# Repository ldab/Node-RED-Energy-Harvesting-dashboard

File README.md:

# Node-RED-Energy-Harvesting-dashboard

Node-RED Energy Harvesting dashboard example, weather forecast, temperature and humidty measurement. MQTT, ESP32, u-blox NINA-W10, HTU21D, IBM Cloud, CloudMQTT

## Sumary

1. [How to build PlatformIO based project](/README.md#How-to-build-PlatformIO-based-project)
2. [TODO](/README.md#TODO)
3. [Energy Harvesting](/README.md#Energy-Harvesting)
4. [MQTT Broker](/README.md#MQTT-Broker)
5. [IBM Node-RED Hosting](/README.md#IBM-Node-RED-Hosting)
6. [Node-RED Flow](/README.md#Node-RED-Flow)
7. [OpenWeatherMap API](/README.md#OpenWeatherMap-API)
8. [Node-RED Notification](/README.md#Node-RED-Notification)
9. [Programming](/README.md#Programming)
10. [Calibrating ADC for ESP32](/README.md#Calibrating-ADC-for-ESP32)
11. [Partition Table and Flash size](/README.md#Partition-Table-and-Flash-size)
12. [Erase Flash](/README.md#Erase-Flash)
13. [Power Measurement](/README.md#Power-Measurement)
14. [PCB](/README.md#PCB)
15. [Final Thoughts or Improvements](/README.md#Final-Thoughts-or-Impovements)
16. [Credits](/README.md#Credits)

## How to build PlatformIO based project

* More information can be found on their comprehensive [Docs](https://docs.platformio.org/en/latest/ide/vscode.html). But Basically:

  0. Download and install official Microsoft Visual Studio Code. PlatformIO IDE is built on top of it
  1. **Open** VSCode Package Manager
  2. **Search** for official `platformio-ide` [extension](https://marketplace.visualstudio.com/items?itemName=platformio.platformio-ide)
  3. **Install** PlatformIO IDE.

## TODO

- [x] More detailed IBM deploy;
- [ ] Details on the flows;
- [x] Node to be installed;
- [ ] Energy Harvesting details;

## Energy Harvesting

### Energy Budget

#### While Communicating

Component | ~Typ mA
----------|--------
NINA-W102 |120

#### While Sleep (TPL5110)

Component | ~Typ μA
----------|--------
TPL5110   |0.035
Cap leak  |30
LDO       |1
Passive   |5

* The code takes in average 2000ms to execute;
* Wakes up every hour;
* 10 hours of charging soruce;

## MQTT Broker

The MQTT Broker used is [CloudMQTT](https://www.cloudmqtt.com/) they offer Free accounts 😉 that works just fine.

## IBM Node-RED Hosting

The process was a bit tedious and took a while to get it properly running as of today (2019/06/15) the information provided on the tutorial had few broken links.

[https://nodered.org/docs/platforms/bluemix](https://nodered.org/docs/platforms/bluemix)

1. Sign-up/Log in to [https://cloud.ibm.com/](https://cloud.ibm.com/);
2. Using the top search bar, search for `Node-RED Starter`;
3. Fill the required fields, `App name`, `Host name`, etc...
4. Select `Lite` for `SDK for Node.js` and `Cloudant`, those are free, you can upgrade later if required;
5. Click `Create` at the bottom right, the circle will spin, take few seconds;
6. You will be redirected to the next page and should see `running` when everything is ready for use:

7. Go to your App URL, something like [http://AppName.eu-gb.mybluemix.net](http://AppName.eu-gb.mybluemix.net) and complete the initial set-up;
8. The Node-Red GUI Flow Editor is available at [http://AppName.eu-gb.mybluemix.net/red](http://AppName.eu-gb.mybluemix.net/red)

* After installing the Node desbribed below, Your Node-red Dashboard is available at [http://AppName.eu-gb.mybluemix.net/ui](http://AppName.eu-gb.mybluemix.net/ui)

## Node-RED Flow

### Install required nodes

* Menu -> Manage Palette -> Install tab. You will need `node-red-node-openweathermap` and `node-red-dashboard`

### Import Node example

* Copy the flow below and import to your Nore-RED available at `yournode.eu-gb.mybluemix.net/red` Import > Clipboard, paste it.

You will find the flow.json [here](./Node-RED%20flow/flows.json).

### Cloudant Credentials for cleaning database

* Generally Cloudant autheticate via IBM cloud therefore we need to create new Credentials and use the username and password for authentication on the `delet inputs on database` node.

## OpenWeatherMap API

* In order to get the weather forecast information for the OpenWeatherMap node, you will need to get your API at [https://openweathermap.org/api](https://openweathermap.org/api)
* Then define your location and the information you would like to show on the "Forecast String" node:
```
{
  "coord":{"lon":139,"lat":35},
  "sys":{"country":"JP","sunrise":1369769524,"sunset":1369821049},
  "weather":[{"id":804,"main":"clouds","description":"overcast clouds","icon":"04n"}],
  "main":{"temp":289.5,"humidity":89,"pressure":1013,"temp_min":287.04,"temp_max":292.04},
  "wind":{"speed":7.31,"deg":187.002},
  "rain":{"3h":0},
  "clouds":{"all":92},
  "dt":1369824698,
  "id":1851632,
  "name":"Shuzenji",
  "cod":200
}
```

## Node-RED Notification

* Via the `catch` node, you can enable notification, for your phone for example. Below I have quickly show few options:

1. Email

  * Use the `email` output, configured with your email provider info;

2. PushSafer

  * Offers several customizations, sound, vibration, icons, etc:
  * GET request url: `https://www.pushsafer.com/api?k=YOURKEY&c=%23ff0000&v=1&a=1&m={{payload}}`

5. Twilio SMS

  * SMS API, built-in to the Node-RED and IBM example;

6. IFTT

  * If this than that, with android and iOS apps can be accesible via webhooks;
  * GET `https://maker.ifttt.com/trigger/YOUR_EVENT/with/key/YOUR_KEY?value1=MESSAGE`

## NINA-W1 Programming

* An external 3.3V UART/USB Converter is required in combination with jumper configuration and button pressing:
  1. Remove the 2 jumpers and set it to `Flash` Position:

  2. Power or reset the board while keeping `BOOT` low/pressed.

* In order to program the Nano Timer `TPL5110` the DIP switch needs to be set **before** connecting power/supercap.

## Calibrating ADC for ESP32

* ADC on ESP32 has been reported being innacurate, therefore one can use ```adc2_vref_to_gpio( GPIO_NUM_25 );``` to route `Vref` to `GPIO_NUM_25` that can be measured over `NINA PIN 16 -> R7` in order to calibrate during ADC measurement.
* Calling for `esp_adc_cal_characterize(ADC_UNIT_1, ADC_ATTEN_DB_6, ADC_WIDTH_BIT_11, Vref, adc_chars);`

## Partition Table and Flash size

* You can create a custom partitions table (CSV) following [ESP32 Partition Tables](https://docs.espressif.com/projects/esp-idf/en/latest/api-guides/partition-tables.html) documentation.

* Partitions examples are available at [GitHub arduino-esp32](https://github.com/espressif/arduino-esp32/tree/master/tools/partitions)

* `minimal.csv` is the default defined on [nina_w10.json](https://github.com/platformio/platform-espressif32/blob/master/boards/nina_w10.json) however I changed it in order to free some space up used by spiffs found on `partitions_custom.csv` [here](./partitions_custom.csv)
  * No OTA;
  * No SPIFFS;
  * No EEPROM;

## Erase Flash

`pio run -t erase` - > all data will be replaced with 0xFF bytes.

## Power Measurement

* The overall power/current can be measure by diconeting the Storage element and connecting the meter in series;
* Alternativelly, to analyze NINA-W1 power profile, remove `Vbat` jumper and measure the current on the following position:

## PCB

### Schematic

### Enclosure

### BOM

[BOM u-blox E-PEAS](./extras/BOM.csv)

## Final Thoughts or Improvements

* Use 3.0V LDO, HT7830;
* Replace LDO for a smaller drop-out voltage or lower power-down current;
* Use a Buck/Boost converter instead of LDO in order to discharge super cap until 2.8V;

## Credits

GitHub Shields and Badges created with [Shields.io](https://github.com/badges/shields/)

Weather information from [OpenWeatherMap](https://openweathermap.org)

Webcam picture from [webcam.travel](https://www.webcams.travel)

Adafruit HTU21D GitHub [Library](https://github.com/adafruit/Adafruit_HTU21DF_Library)

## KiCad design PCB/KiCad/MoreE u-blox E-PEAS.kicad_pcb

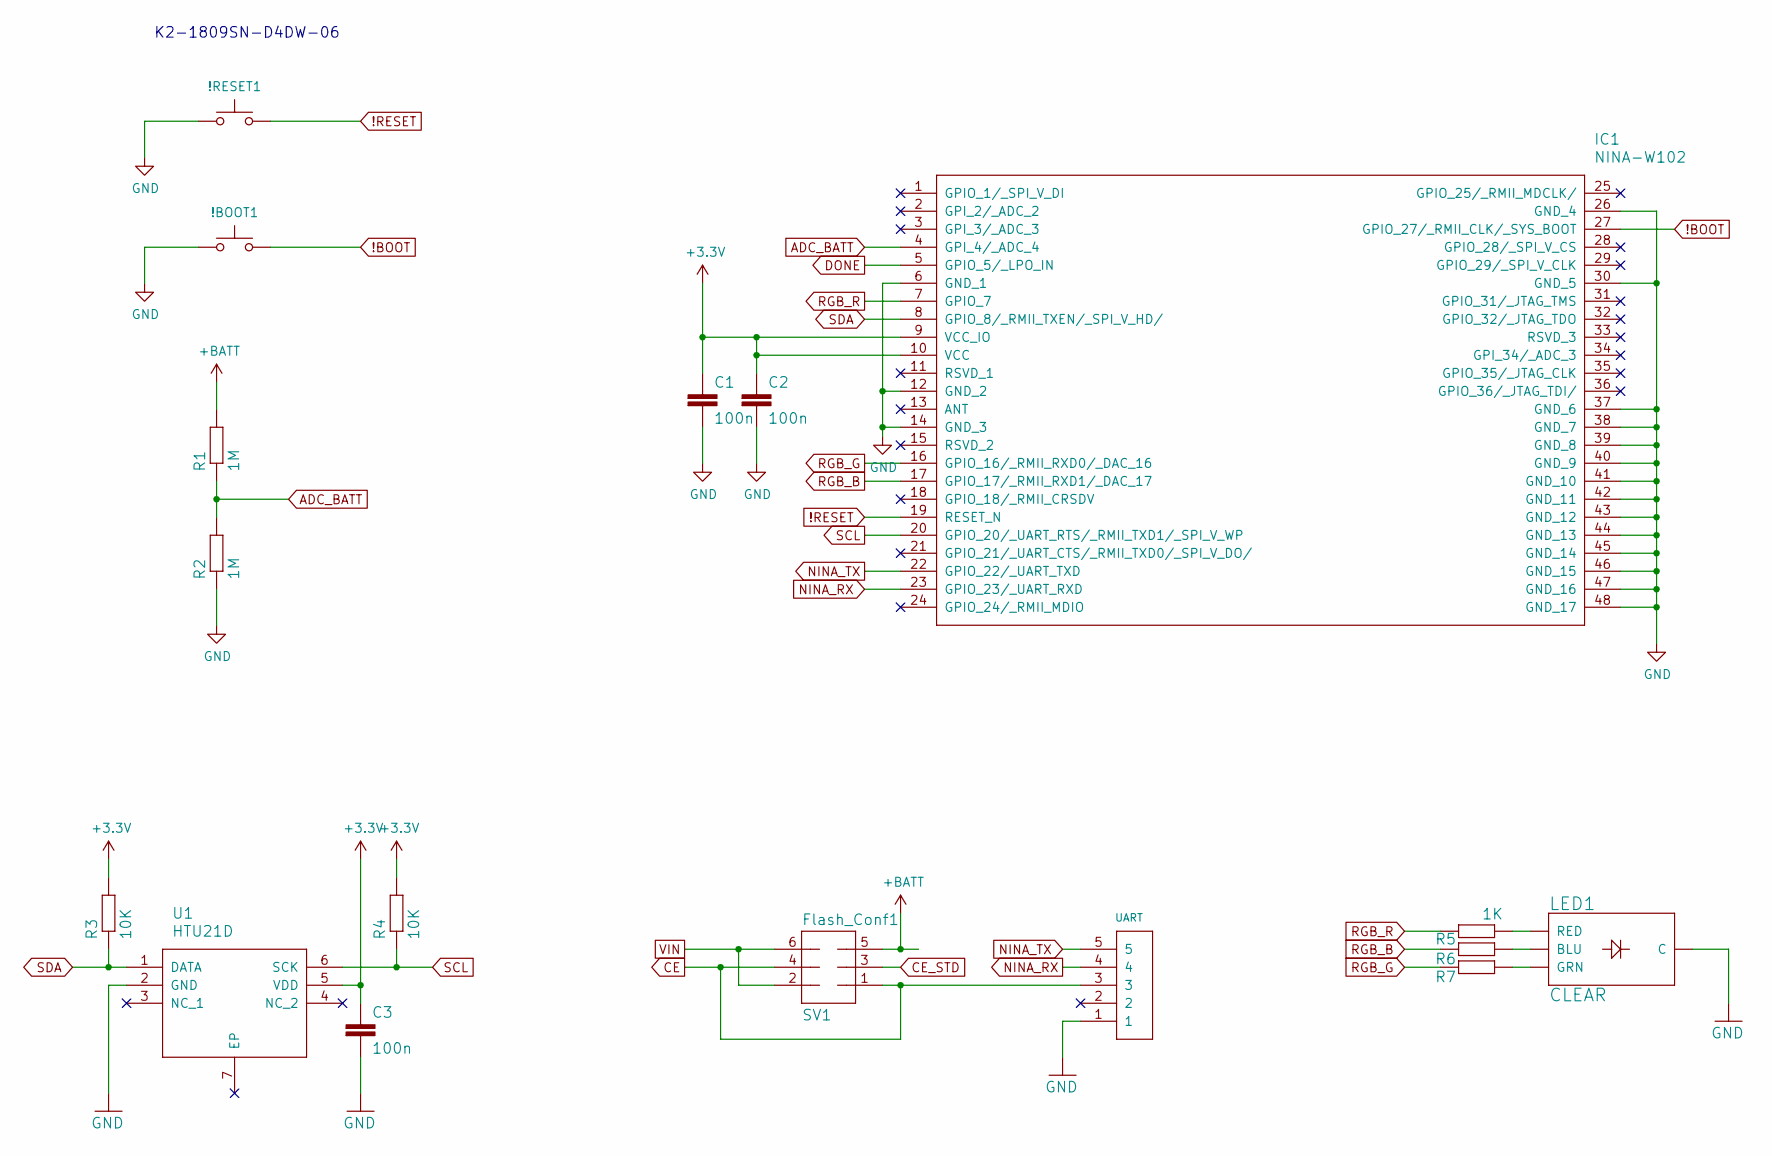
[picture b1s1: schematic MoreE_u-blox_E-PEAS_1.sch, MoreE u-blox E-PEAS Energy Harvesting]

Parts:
!BOOT1: SW_Push_KMR2; SW_Push_1P1T_NO_CK_KMR2
!RESET1: SW_Push_KMR2; SW_Push_1P1T_NO_CK_KMR2
C1, C2, C3: 100n; C_0805_2012Metric
Flash_Conf1: SV1; PinHeader_2x03_P2.54mm_Vertical
IC1: NINA-W102; NINAW102
LED1: CLEAR; LED_D5.0mm-4_RGB
R1, R2: 1M; R_0805_2012Metric
R3, R4: 10K; R_0805_2012Metric
R5, R6, R7: 1K; R_0805_2012Metric
SV2: UART; PinHeader_1x05_P2.54mm_Vertical
U1: HTU21D; DFN-6-1EP_3x3mm_P1mm_EP1.5x2.4mm

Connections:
!BOOT: !BOOT1.2, IC1.27 (GPIO_27/_RMII_CLK/_SYS_BOOT)
!RESET: !RESET1.2, IC1.19 (RESET_N)
+3V3: C1.1, C2.1, C3.1, IC1.9 (VCC_IO), IC1.10 (VCC), R3.2, R4.2, U1.5 (VDD); also elsewhere on the board
+BATT: Flash_Conf1.5, R1.2; also elsewhere on the board
ADC_BATT: IC1.4 (GPI_4/_ADC_4), R1.1, R2.2
CE: Flash_Conf1.1, Flash_Conf1.4, SV2.3; also elsewhere on the board
CE_STD: Flash_Conf1.3; also elsewhere on the board
DONE: IC1.5 (GPIO_5/_LPO_IN); also elsewhere on the board
GND: !BOOT1.1, !RESET1.1, C1.2, C2.2, C3.2, IC1.6 (GND_1), IC1.12 (GND_2), IC1.14 (GND_3), IC1.26 (GND_4), IC1.30 (GND_5), IC1.37 (GND_6), IC1.38 (GND_7), IC1.39 (GND_8), IC1.40 (GND_9), IC1.41 (GND_10), IC1.42 (GND_11), IC1.43 (GND_12), IC1.44 (GND_13), IC1.45 (GND_14), IC1.46 (GND_15), IC1.47 (GND_16), IC1.48 (GND_17), LED1.2 (C), R2.1, SV2.1, U1.2 (GND); also elsewhere on the board
NINA_RX: IC1.23 (GPIO_23/_UART_RXD), SV2.4
NINA_TX: IC1.22 (GPIO_22/_UART_TXD), SV2.5
unnamed: LED1.1 (RED), R5.1
unnamed: LED1.3 (GRN), R7.1
unnamed: LED1.4 (BLU), R6.1
RGB_B: IC1.17 (GPIO_17/_RMII_RXD1/_DAC_17), R6.2
RGB_G: IC1.16 (GPIO_16/_RMII_RXD0/_DAC_16), R7.2
RGB_R: IC1.7 (GPIO_7), R5.2
SCL: IC1.20 (GPIO_20/_UART_RTS/_RMII_TXD1/_SPI_V_WP), R4.1, U1.6 (SCK)
SDA: IC1.8 (GPIO_8/_RMII_TXEN/_SPI_V_HD/), R3.1, U1.1 (DATA)
VIN: Flash_Conf1.2, Flash_Conf1.6; also elsewhere on the board

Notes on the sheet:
K2-1809SN-D4DW-06

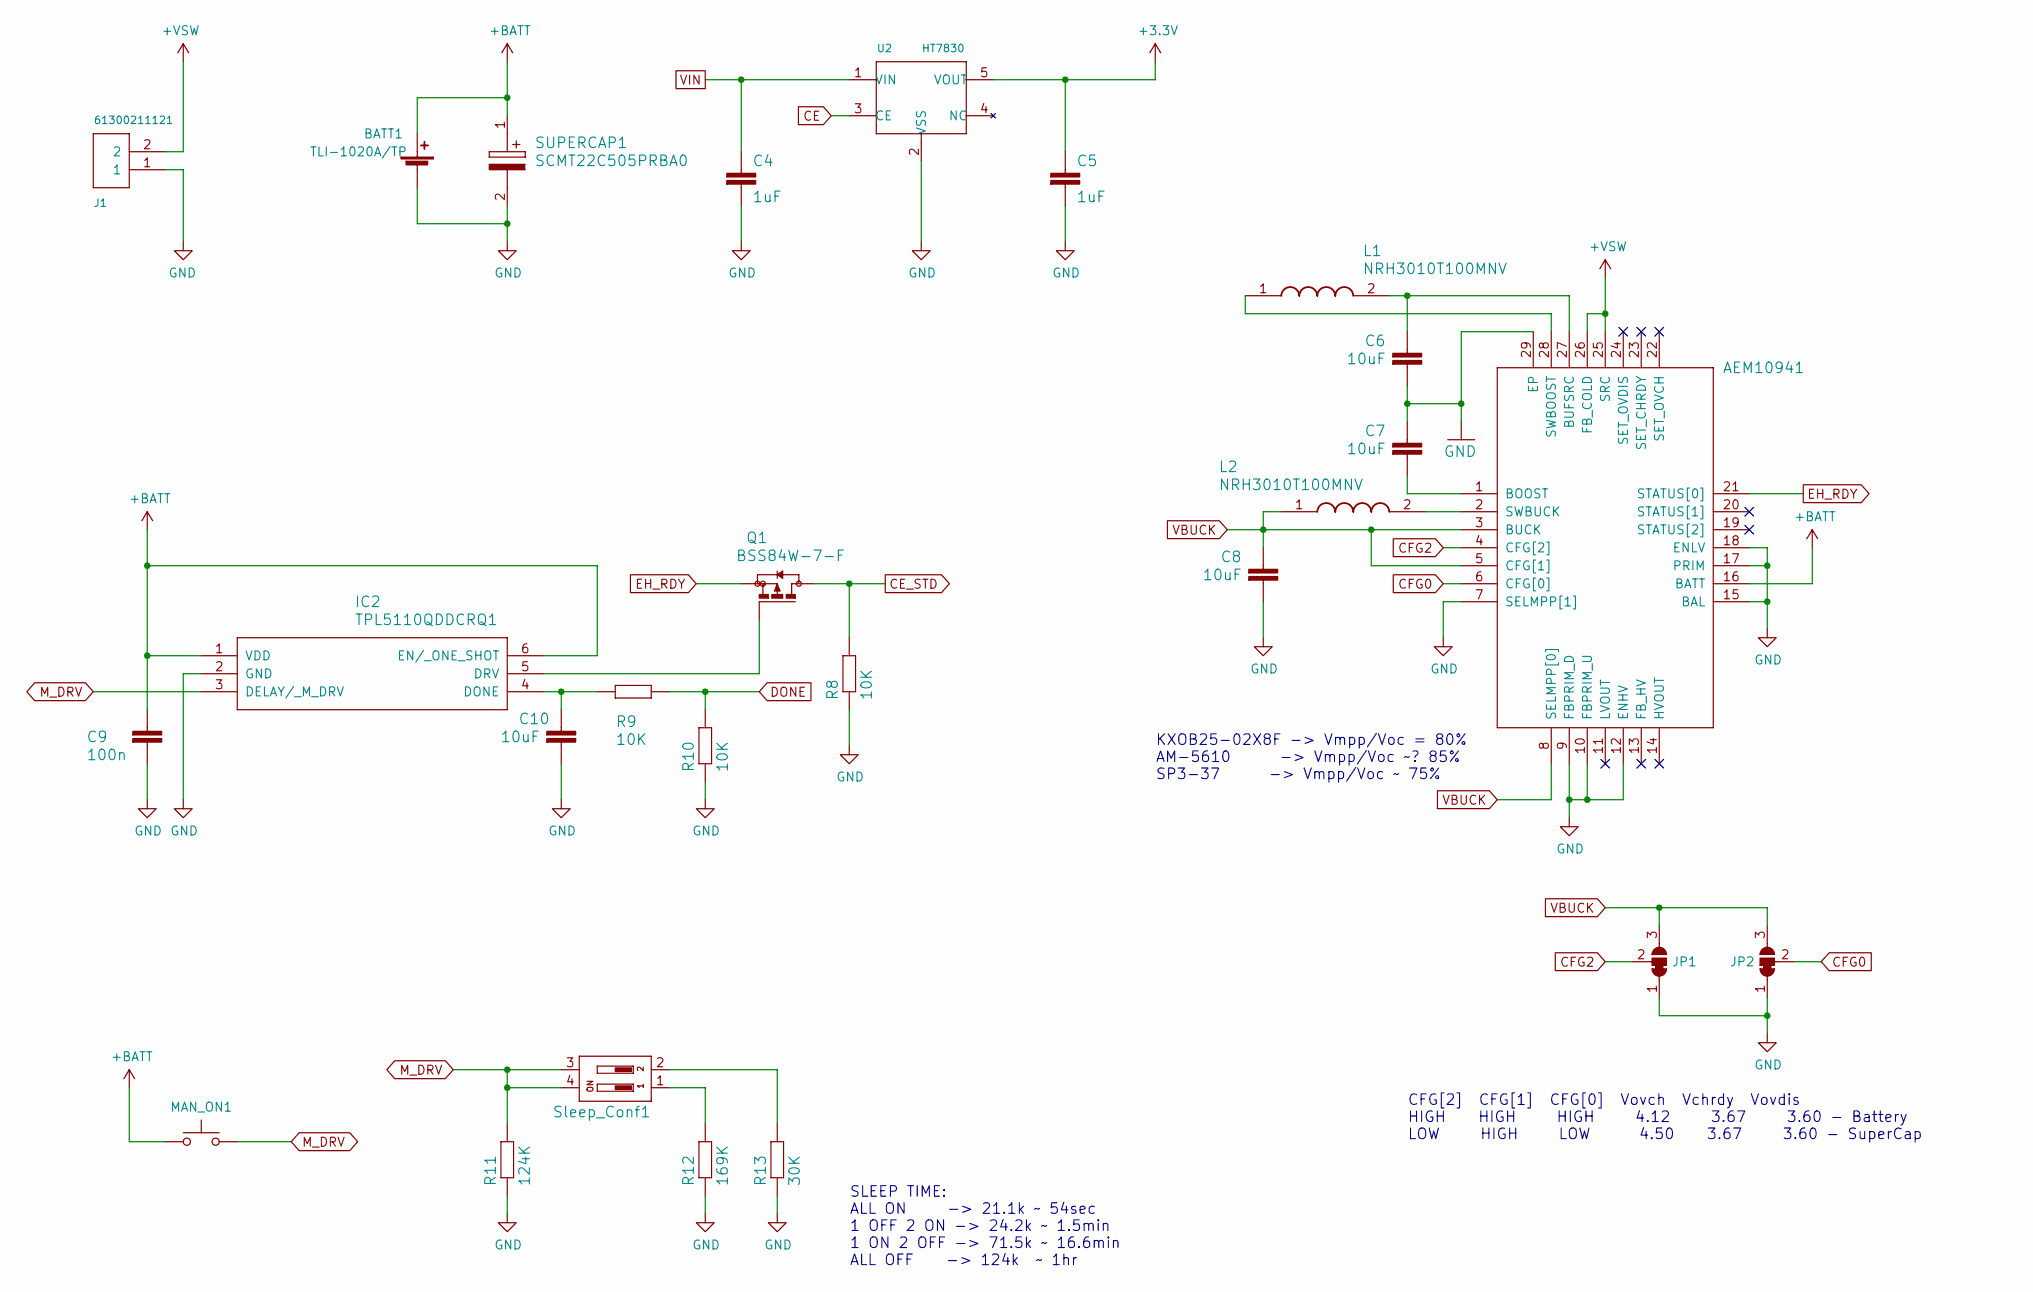
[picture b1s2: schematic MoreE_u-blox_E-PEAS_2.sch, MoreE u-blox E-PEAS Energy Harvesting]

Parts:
AEM10941: AEM10941; QFN-28-1EP_5x5mm_P0.5mm_EP3.35x3.35mm
BATT1: TLI-1020A/TP
C4, C5: 1uF; C_0805_2012Metric
C6, C7, C8, C10: 10uF; C_0805_2012Metric
C9: 100n; C_0805_2012Metric
IC2: TPL5110QDDCRQ1; SOT-23-6
J1: 61300211121; PinHeader_1x02_P2.54mm_Vertical
JP1, JP2: SolderJumper_3_Bridged12; SolderJumper-3_P1.3mm_Bridged12_RoundedPad1.0x1.5mm
L1, L2: NRH3010T100MNV; L_Taiyo-Yuden_NRH30xx
MAN_ON1: SW_Push_KMR2; SW_Push_1P1T_NO_CK_KMR2
Q1: BSS84W-7-F; SOT-323_SC-70
R8, R9, R10: 10K; R_0805_2012Metric
R11: 124K; R_0805_2012Metric
R12: 169K; R_0805_2012Metric
R13: 30K; R_0805_2012Metric
SUPERCAP1: SCMT22C505PRBA0
Sleep_Conf1: Sleep Conf; SW_DIP_SPSTx02_Slide_9.78x7.26mm_W7.62mm_P2.54mm
U2: HT7830; SOT-23-5

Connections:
+3V3: C5.1, U2.5 (VOUT); also elsewhere on the board
+BATT: AEM10941.16 (BATT), BATT1.1 (+), C9.1, IC2.1 (VDD), IC2.6 (EN/_ONE_SHOT), MAN_ON1.1, SUPERCAP1.1 (-); also elsewhere on the board
+VSW: AEM10941.25 (SRC), AEM10941.26 (FB_COLD), J1.2
CE: U2.3 (CE); also elsewhere on the board
CE_STD: Q1.3 (D), R8.2; also elsewhere on the board
CFG0: AEM10941.6 (CFG[0]), JP2.2 (C)
CFG2: AEM10941.4 (CFG[2]), JP1.2 (C)
DONE: R9.2, R10.2; also elsewhere on the board
EH_RDY: AEM10941.21 (STATUS[0]), Q1.2 (S)
GND: AEM10941.7 (SELMPP[1]), AEM10941.9 (FBPRIM_D), AEM10941.10 (FBPRIM_U), AEM10941.12 (ENHV), AEM10941.15 (BAL), AEM10941.17 (PRIM), AEM10941.18 (ENLV), AEM10941.29 (EP), BATT1.2 (-), C4.2, C5.2, C6.2, C7.1, C8.2, C9.2, C10.2, IC2.2 (GND), J1.1, JP1.1 (A), JP2.1 (A), R8.1, R10.1, R11.1, R12.1, R13.1, SUPERCAP1.2 (+), U2.2 (VSS); also elsewhere on the board
M_DRV: IC2.3 (DELAY/_M_DRV), MAN_ON1.2, R11.2, Sleep_Conf1.3, Sleep_Conf1.4
unnamed: AEM10941.1 (BOOST), C7.2
unnamed: AEM10941.2 (SWBUCK), L2.2
unnamed: AEM10941.27 (BUFSRC), C6.1, L1.2
unnamed: AEM10941.28 (SWBOOST), L1.1
unnamed: C10.1, IC2.4 (DONE), R9.1
unnamed: IC2.5 (DRV), Q1.1 (G)
unnamed: R12.2, Sleep_Conf1.1
unnamed: R13.2, Sleep_Conf1.2
VBUCK: AEM10941.3 (BUCK), AEM10941.5 (CFG[1]), AEM10941.8 (SELMPP[0]), C8.1, JP1.3 (B), JP2.3 (B), L2.1
VIN: C4.1, U2.1 (VIN); also elsewhere on the board

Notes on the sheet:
SLEEP TIME: ALL ON -> 21.1k ~~ 54sec 1 OFF 2 ON -> 24.2k ~~ 1.5min 1 ON 2 OFF -> 71.5k ~~ 16.6min ALL OFF -> 124k ~~ 1hr
CFG[2] CFG[1] CFG[0] Vovch Vchrdy Vovdis HIGH HIGH HIGH 4.12 3.67 3.60 - Battery LOW HIGH LOW 4.50 3.67 3.60 - SuperCap
KXOB25-02X8F -> Vmpp/Voc = 80% AM-5610 -> Vmpp/Voc ~~? 85% SP3-37 -> Vmpp/Voc ~~ 75%

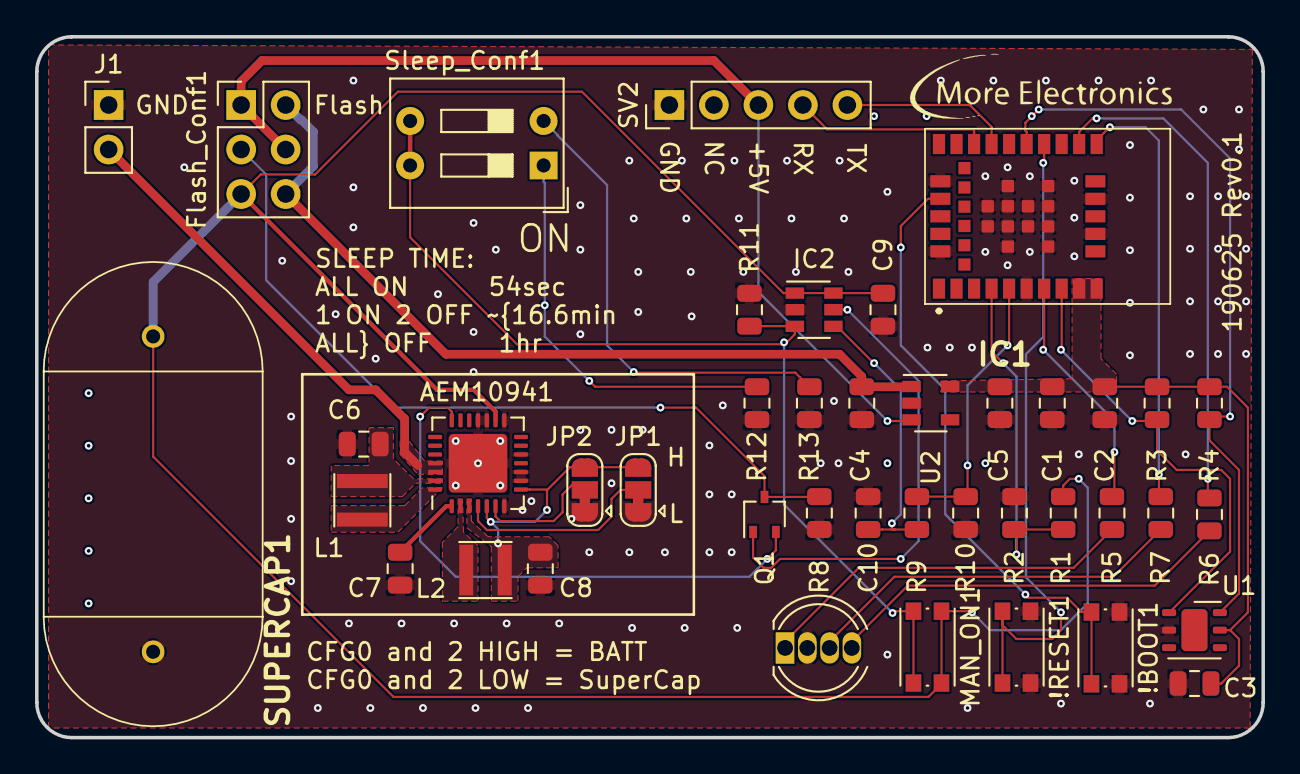
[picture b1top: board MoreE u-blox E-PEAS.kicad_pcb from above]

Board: 2 copper layers, 70.0 x 40.0 mm, 42 parts (0 on the bottom side), 34 nets.

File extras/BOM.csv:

Id,Designator,Package,Quantity,Designation,Supplier and ref,Column1,_1
1,G***,MoreE,1,LOGO,,,
2,SV2,PinHeader_1x05_P2.54mm_Vertical,1,UART,,,
3,"JP1,JP2",SolderJumper-3_P1.3mm_Bridged12_RoundedPad1.0x1.5mm,2,SolderJumper_3_Bridged12,,,
4,"MAN_ON1,!RESET1,!BOOT1",SW_Push_1P1T_NO_CK_KMR2,3,SW_Push_KMR2,,,
5,"L2,L1",L_Taiyo-Yuden_NRH30xx,2,NRH3010T100MNV,,,
6,"C1,C2,C3,C9",C_0805_2012Metric,4,100n,,,
7,"C4,C5",C_0805_2012Metric,2,1uF,,,
8,"C6,C7,C8,C10",C_0805_2012Metric,4,10uF,,,
9,IC1,NINAW102,1,NINA-W102,,,
10,IC2,SOT-23-6,1,TPL5110QDDCRQ1,,,
11,J1,PinHeader_1x02_P2.54mm_Vertical,1,61300211121,,,
12,LED1,LED_D5.0mm-4_RGB,1,CLEAR,,,
13,AEM10941,QFN-28-1EP_5x5mm_P0.5mm_EP3.35x3.35mm,1,AEM10941,,,
14,Q1,SOT-323_SC-70,1,BSS84W-7-F,,,
15,"R1,R2",R_0805_2012Metric,2,1M,,,
16,"R3,R4,R8,R9,R10",R_0805_2012Metric,5,10K,,,
17,"R5,R6,R7",R_0805_2012Metric,3,1K,,,
18,R11,R_0805_2012Metric,1,124K,,,
19,R12,R_0805_2012Metric,1,169K,,,
20,R13,R_0805_2012Metric,1,30K,,,
21,Sleep_Conf1,SW_DIP_SPSTx02_Slide_9.78x7.26mm_W7.62mm_P2.54mm,1,Sleep Conf,,,
22,SUPERCAP1,SCMT22C505PRBA0,1,SCMT22C505PRBA0,,,
23,Flash_Conf1,PinHeader_2x03_P2.54mm_Vertical,1,SV1,,,
24,U1,DFN-6-1EP_3x3mm_P1mm_EP1.5x2.4mm,1,HTU21D,,,
25,U2,SOT-23-5,1,HT7830,,,

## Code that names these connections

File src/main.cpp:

/******************************************************************************

Node-RED Energy Harvesting dashboard example, weather forecast, temperature and humidty measurement. MQTT, ESP32, u-blox NINA-W10, HTU21D, IBM Cloud, CloudMQTT 
Leonardo Bispo
June - 2019
https://github.com/ldab/Node-RED-Energy-Harvesting-dashboard

Distributed as-is; no warranty is given.

This example tries to implement some key functions and key PIN atributes in order
to get you started with using Arduino and the espresif ESP32 board u-blox NINA-W10

******************************************************************************/

#include "Arduino.h"
#include "Wire.h"
#include <Ticker.h>
#include <Adafruit_HTU21DF.h>
#include <WiFi.h>

#include "esp_wifi.h"
#include <driver/adc.h>
#include <esp_adc_cal.h>

extern "C" {
	#include "freertos/FreeRTOS.h"
	#include "freertos/timers.h"
}

#include <AsyncMqttClient.h>

// Enable Debug interface and serial prints over UART1
#define DEGUB_NINA
#define WIFI_SSID     ""
#define WIFI_PASSWORD ""
#define MQTT_HOST     ""
#define MQTT_PORT     17603
#define USERNAME      ""
#define PASSWORD      ""

// Connection timeout, if too high capacitor may discharge before connecting Bt(seconds) = [C(Vcapmax - Vcapmin)/I]
#define CON_TIMEOUT   10*1000                     // milliseconds

// Not using Deep Sleep on PCB because TPL5110 timer takes over.
#define TIME_TO_SLEEP (uint64_t)50*60*1000*1000   // microseconds

/******************     EVK-NINA-W10 PIN Definition      ************************************
 * .platformio\packages\framework-arduinoespressif32\variants\nina_w10
LED_GREEN = 33;
LED_RED   = 23;
LED_BLUE  = 21;
SW1       = 33;
SW2       = 27;

TX        = 1;
RX        = 3;

SDA       = 12;
SCL       = 13;
***************************************************************************************/

// Re-assign pins for PCB.

#define _SDA          21
#define _SCL          22
#define RGB_R         33
#define RGB_G         25
#define RGB_B         26
#define DONE          32
#define BATT          36                        //ADC1 CHANNEL 0 *ADC2 chanel can't be used in conjunction with Wi-Fi https://docs.espressif.com/projects/esp-idf/en/latest/api-reference/peripherals/adc.html

#ifdef DEGUB_NINA
  #define DBG_NINA(x) Serial.println(x)
#else 
  #define DBG_NINA(...)
#endif

// Initialize the Temperature and Humidity Sensor HTU21D
Adafruit_HTU21DF htu = Adafruit_HTU21DF();

AsyncMqttClient mqttClient;
TimerHandle_t   mqttReconnectTimer;
TimerHandle_t   wifiReconnectTimer;

// Create timers using Ticker library
Ticker blinkIt;

// Create functions prior to calling them as .cpp files are differnt from Arduino .ino
void blinky     ( void );
void readSensor ( void );
void connectWiFi( void );
void connectMQTT( void );
void deep_sleep ( void );

// Declare Global variables
float t = NAN;
float h = NAN;

uint8_t statusLED = RGB_B;

void RGB_off( void )
{
  digitalWrite( RGB_R, LOW );
  digitalWrite( RGB_G, LOW );
  digitalWrite( RGB_B, LOW );
}

void onMqttConnect(bool sessionPresent)
{
  // Get temperature and humidity;
  readSensor();

  // Publish Temperature
  String t_string = String( t,1 );
  const char* t_send = t_string.c_str();
  uint16_t packetIdPubTemp = mqttClient.publish( "temp_office", 0, false, t_send );

  // No delay result in no message sent.
  delay(200);

  // Publish Humidity
  String h_string = String(h,1);
  const char* h_send = h_string.c_str();
  uint16_t packetIdPubHum = mqttClient.publish( "hum_office", 0, false, h_send );

  // No delay result in no message sent.
  delay(200);

  adc1_config_width( ADC_WIDTH_BIT_11 );                          // Reduce ADC resolution due to reported noise on 12 bits
  adc1_config_channel_atten( ADC1_CHANNEL_0, ADC_ATTEN_DB_11 );   // -11dB attenuation (ADC_ATTEN_DB_11) gives full-scale voltage 3.6V

  esp_adc_cal_characteristics_t *adc_chars = new esp_adc_cal_characteristics_t;
  esp_adc_cal_characterize(ADC_UNIT_1, ADC_ATTEN_DB_11, ADC_WIDTH_BIT_11, 1089, adc_chars);  // rout vRef in order to calibrate: 

  // Average and smooth ADC
  int batt = 0;
  uint8_t i = 0;
  for( i = 0; i < 5; i++)
    batt += adc1_get_raw( ADC1_CHANNEL_0 );

  // Publish Battery
  float b  = (float)batt/i * 2 * 3.6 / 2048;
  String b_string = String( b, 2 );
  DBG_NINA( "Battery = " + b_string + "V");
  const char* b_send = b_string.c_str();
  uint16_t packetIdPubBatt = mqttClient.publish( "batt_office", 0, false, b_send );

  // No delay result in no message sent.
  delay(200);

  if( !packetIdPubTemp || !packetIdPubHum || !packetIdPubBatt )
  {
    DBG_NINA( "Sending Failed!" );
  }

  deep_sleep();
}

void deep_sleep()
{
  // Send DONE to TPL5110 and go to sleep
  pinMode( DONE, OUTPUT );
  digitalWrite( DONE, HIGH );

  // Keep deep sleep as sanity check in case it fails to detect DONE.
  delay( 1000 );

  DBG_NINA( "Going to sleep after: " + String( millis() ) + "ms" );

  // Turn Wifi/BLE off  
  WiFi.mode(WIFI_OFF);
  btStop();
  esp_wifi_deinit();

  // Enable timer wake up
  esp_sleep_enable_timer_wakeup( TIME_TO_SLEEP );
  esp_deep_sleep_start();
}

void setup()
{
  // Measure GPIO in order to determine Vref
  //adc2_vref_to_gpio( GPIO_NUM_25 );
  //delay(5000);

  // Define pins on the NINA board
  pinMode( RGB_R, OUTPUT );
  pinMode( RGB_G, OUTPUT );
  pinMode( RGB_B, OUTPUT );
  RGB_off();

  blinkIt.attach_ms( 200, blinky );

  mqttReconnectTimer = xTimerCreate("mqttTimer", pdMS_TO_TICKS(2000), pdFALSE, (void*)0, reinterpret_cast<TimerCallbackFunction_t>(connectMQTT));
  mqttClient.setCredentials( USERNAME, PASSWORD );
  mqttClient.onConnect (onMqttConnect );
  mqttClient.setServer( MQTT_HOST, MQTT_PORT );

  #ifdef DEGUB_NINA
    Serial.begin(115200);
  #endif

  // SDA and SCL PINS on NINA are different from NODEMCU ESP32, the lib does not allow re-assignement, do it here:
  Wire.begin( _SDA, _SCL );

  if ( !htu.begin() )
  {
    DBG_NINA("Couldn't find sensor!");
    statusLED = RGB_R;
    delay( 600 );
    deep_sleep();
  }

  connectWiFi();
  connectMQTT();

}

void loop()
{

} // end of loop

void readSensor( void )
{
  t = htu.readTemperature();
  h = htu.readHumidity();

  if (! isnan(t)) {  // check if 'is not a number'
    Serial.print("Temp ºC = "); DBG_NINA(t);
  } else { 
    DBG_NINA("Failed to read temperature");
  }
  
  if (! isnan(h)) {  // check if 'is not a number'
    Serial.print("Hum. % = "); DBG_NINA(h);
  } else { 
    DBG_NINA("Failed to read humidity");
  }
  
}

// Toggle LED_Blue
void blinky( void )
{
  bool toggle = digitalRead( statusLED );

  digitalWrite( statusLED, !toggle );
}

void connectWiFi() {
  DBG_NINA("Connecting to Wi-Fi...");
  WiFi.begin(WIFI_SSID, WIFI_PASSWORD);

  while (WiFi.status() != WL_CONNECTED && millis() < CON_TIMEOUT)
  {
    delay(500);
    Serial.print(".");
  }

  if( WiFi.status() != WL_CONNECTED )
  {
    RGB_off();
    statusLED = RGB_R;
    delay( 600 );
    deep_sleep();
  }

  RGB_off();
  statusLED = RGB_G;

  blinkIt.attach_ms( 50, blinky );

  DBG_NINA();
  DBG_NINA("IP address: ");
  DBG_NINA(WiFi.localIP());

}

void connectMQTT() {
  DBG_NINA("Connecting to MQTT...");
  mqttClient.connect();

  while( !mqttClient.connected() && millis() < CON_TIMEOUT )
  {
    delay(250);
    Serial.print(".");
  }

  if( !mqttClient.connected() )
  {
    DBG_NINA("Failed to connect to MQTT Broker");
    deep_sleep();
  }

}

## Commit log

2019-06-14 initial comit
2019-07-05 release node-red flow
2019-07-06 save init time on DB and fix cleaning graph also clean DB
2019-07-06 fix "running for" when device offiline for too long
2019-07-07 Showing offline when disconnected for more than 1 hour
2019-07-08 int overflow and partition table
2019-07-10 include notification on readme
2019-07-20 update dashboard and include enclosure
2019-07-20 dashboard with real values
2019-07-23 IBM deploy details
2019-08-16 updated flow
2019-08-16 pre-release code
2019-08-26 included programming and power details

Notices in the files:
README.md:
License: MIT
